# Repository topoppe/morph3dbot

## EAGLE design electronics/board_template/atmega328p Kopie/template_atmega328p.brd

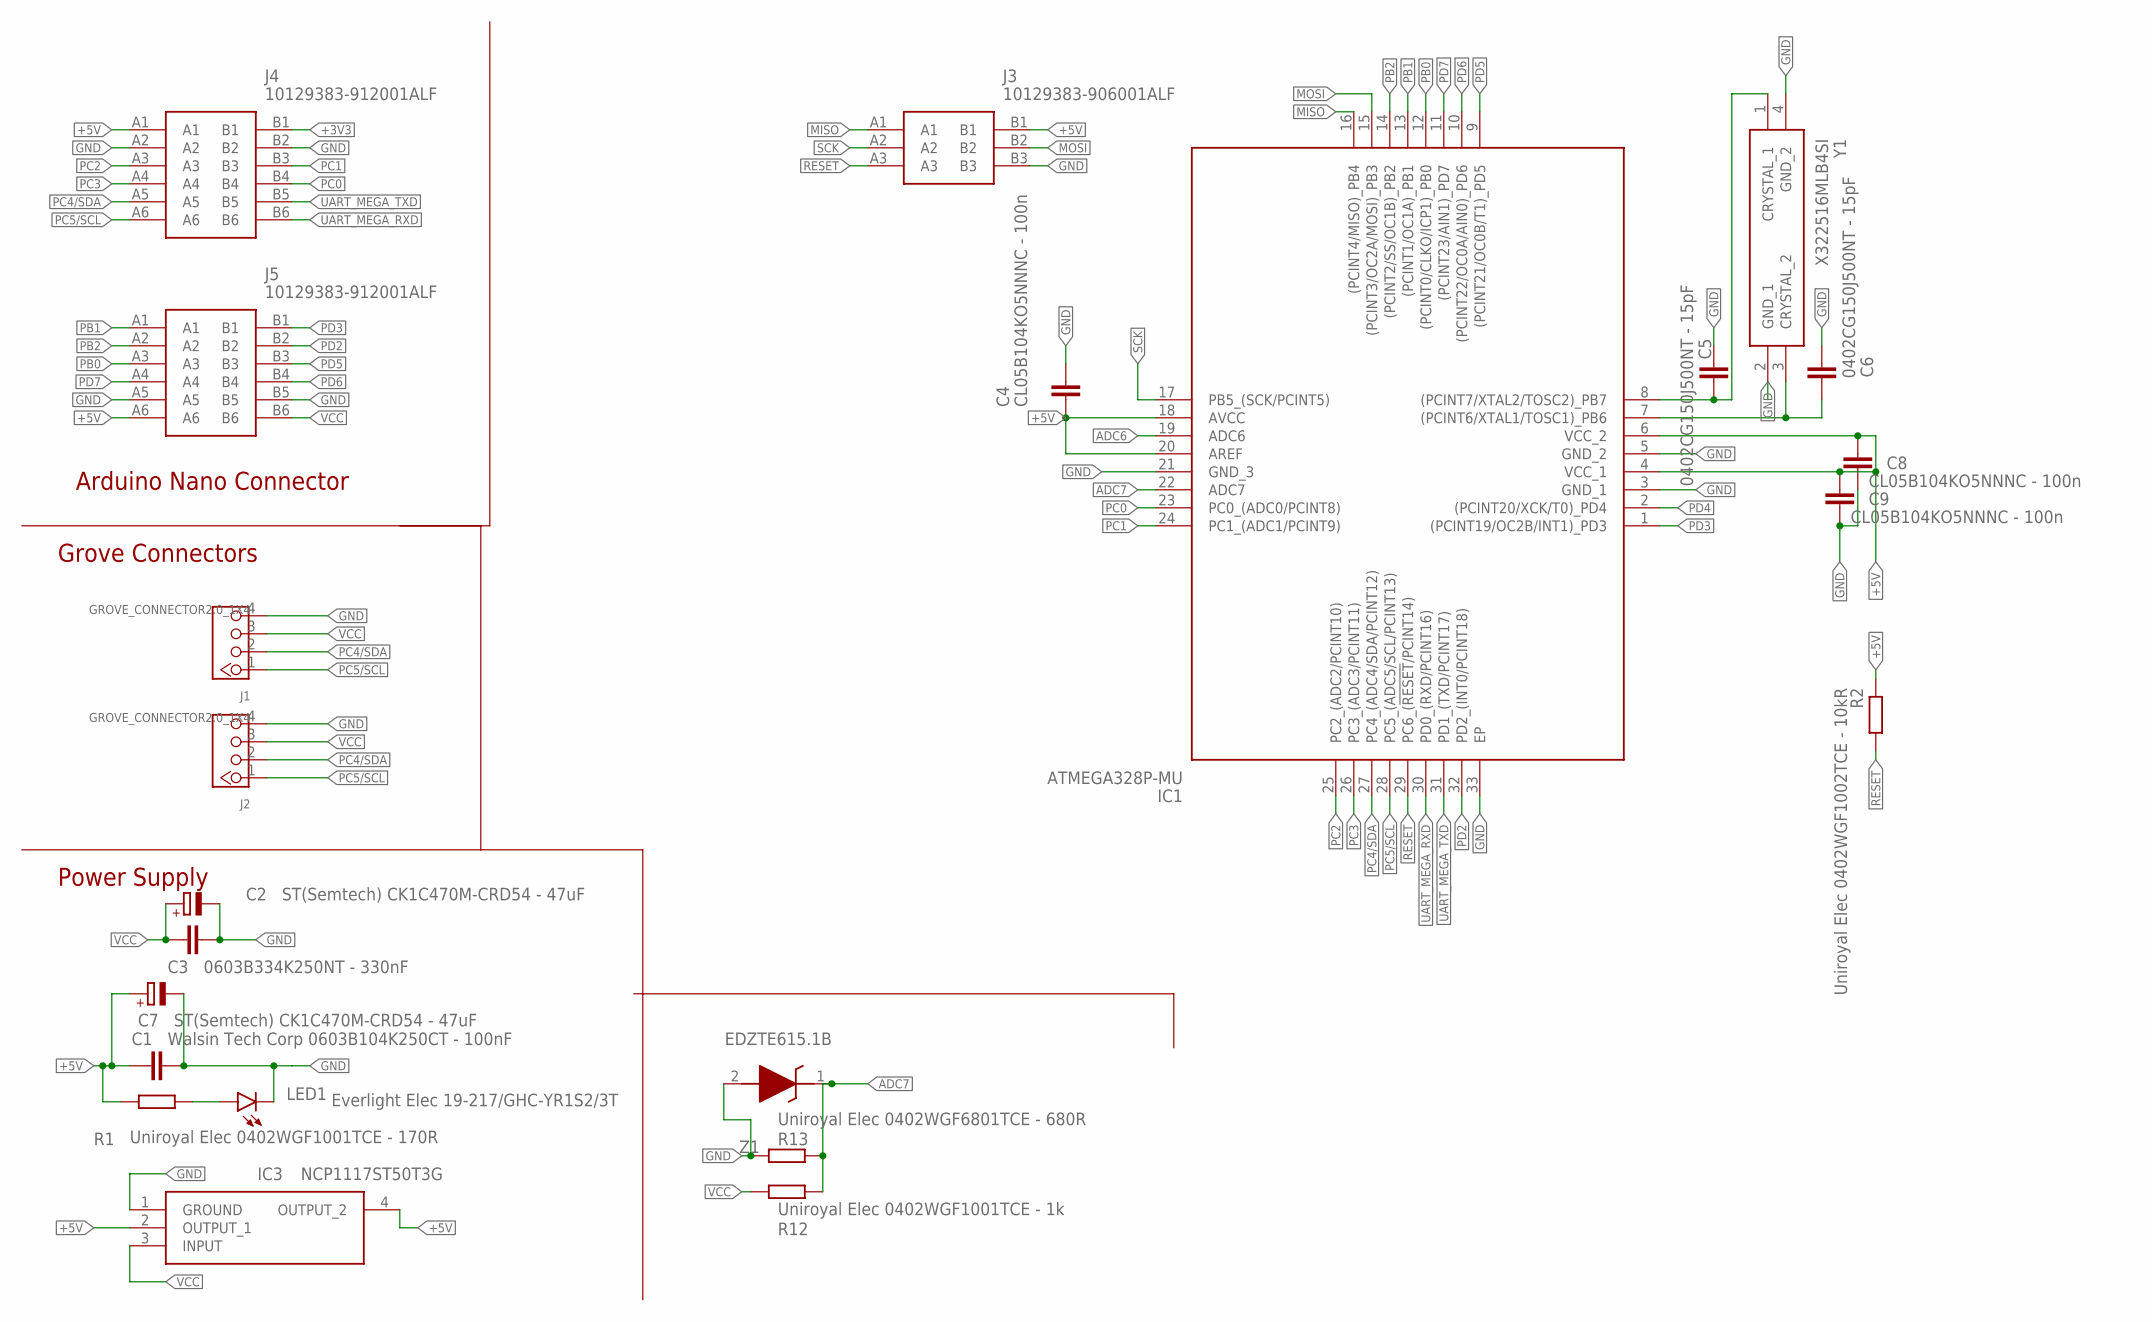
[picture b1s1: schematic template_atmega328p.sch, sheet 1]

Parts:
C1: Walsin Tech Corp 0603B104K250CT - 100nF; C0603
C2, C7: ST(Semtech) CK1C470M-CRD54 - 47uF; PANASONIC_C
C3: 0603B334K250NT - 330nF; C0603
C4, C8, C9: CL05B104KO5NNNC - 100n; C0402
C5, C6: 0402CG150J500NT - 15pF; C0402
IC1: ATMEGA328P-MU; QFN50P500X500X100-33N
IC3: NCP1117ST50T3G; SOT230P700X180-4N@1
J1, J2: GROVE_CONNECTOR2.0_1X4; 2.0_1X4_STRAIGHT
J3: 10129383-906001ALF; 10129383906001ALF
J4, J5: 10129383-912001ALF; 10129383912001ALF
LED1: Everlight Elec 19-217/GHC-YR1S2/3T; CHIPLED_0603
R1: Uniroyal Elec 0402WGF1001TCE - 170R; R0402
R2: Uniroyal Elec 0402WGF1002TCE - 10kR; R0402
R12: Uniroyal Elec 0402WGF1001TCE - 1k; R0402
R13: Uniroyal Elec 0402WGF6801TCE - 680R; R0402
Y1: X322516MLB4SI
Z1: EDZTE615.1B; EMD2

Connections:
+3V3: J4.B1; also elsewhere on the board
+5V: C1.1, C4.1, C7.+, C8.2, C9.2, IC1.4 (VCC_1), IC1.6 (VCC_2), IC1.18 (AVCC), IC1.20 (AREF), IC3.2 (OUTPUT_1), IC3.4 (OUTPUT_2), J3.B1, J4.A1, J5.A6, R1.2, R2.2; also elsewhere on the board
ADC6: IC1.19 (ADC6)
ADC7: IC1.22 (ADC7), R12.1, R13.2, Z1.1 (K)
GND: C1.2, C2.-, C3.1, C4.2, C5.1, C6.1, C7.-, C8.1, C9.1, IC1.3 (GND_1), IC1.5 (GND_2), IC1.21 (GND_3), IC1.33 (EP), IC3.1 (GROUND), J1.4, J2.4, J3.B3, J4.A2, J4.B2, J5.A5, J5.B5, LED1.C, R13.1, Y1.2 (GND_1), Y1.4 (GND_2), Z1.2 (A); also elsewhere on the board
MISO: IC1.16 ((PCINT4/MISO)_PB4), J3.A1
MOSI: IC1.15 ((PCINT3/OC2A/MOSI)_PB3), J3.B2
unnamed: LED1.A, R1.1
unnamed: C5.2, IC1.8 ((PCINT7/XTAL2/TOSC2)_PB7), Y1.1 (CRYSTAL_1)
unnamed: C6.2, IC1.7 ((PCINT6/XTAL1/TOSC1)_PB6), Y1.3 (CRYSTAL_2)
PB0: IC1.12 ((PCINT0/CLKO/ICP1)_PB0), J5.A3
PB1: IC1.13 ((PCINT1/OC1A)_PB1), J5.A1
PB2: IC1.14 ((PCINT2/SS/OC1B)_PB2), J5.A2
PC0: IC1.23 (PC0_(ADC0/PCINT8)), J4.B4
PC1: IC1.24 (PC1_(ADC1/PCINT9)), J4.B3
PC2: IC1.25 (PC2_(ADC2/PCINT10)), J4.A3
PC3: IC1.26 (PC3_(ADC3/PCINT11)), J4.A4
PC4/SDA: IC1.27 (PC4_(ADC4/SDA/PCINT12)), J1.2, J2.2, J4.A5
PC5/SCL: IC1.28 (PC5_(ADC5/SCL/PCINT13)), J1.1, J2.1, J4.A6
PD2: IC1.32 (PD2_(INT0/PCINT18)), J5.B2
PD3: IC1.1 ((PCINT19/OC2B/INT1)_PD3), J5.B1
PD4: IC1.2 ((PCINT20/XCK/T0)_PD4)
PD5: IC1.9 ((PCINT21/OC0B/T1)_PD5), J5.B3
PD6: IC1.10 ((PCINT22/OC0A/AIN0)_PD6), J5.B4
PD7: IC1.11 ((PCINT23/AIN1)_PD7), J5.A4
RESET: IC1.29 (PC6_(!RESET!/PCINT14)), J3.A3, R2.1
SCK: IC1.17 (PB5_(SCK/PCINT5)), J3.A2
UART_MEGA_RXD: IC1.30 (PD0_(RXD/PCINT16)), J4.B6; also elsewhere on the board
UART_MEGA_TXD: IC1.31 (PD1_(TXD/PCINT17)), J4.B5; also elsewhere on the board
VCC: C2.+, C3.2, IC3.3 (INPUT), J1.3, J2.3, J5.B6, R12.2; also elsewhere on the board

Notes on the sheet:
Power Supply
Grove Connectors
Arduino Nano Connector

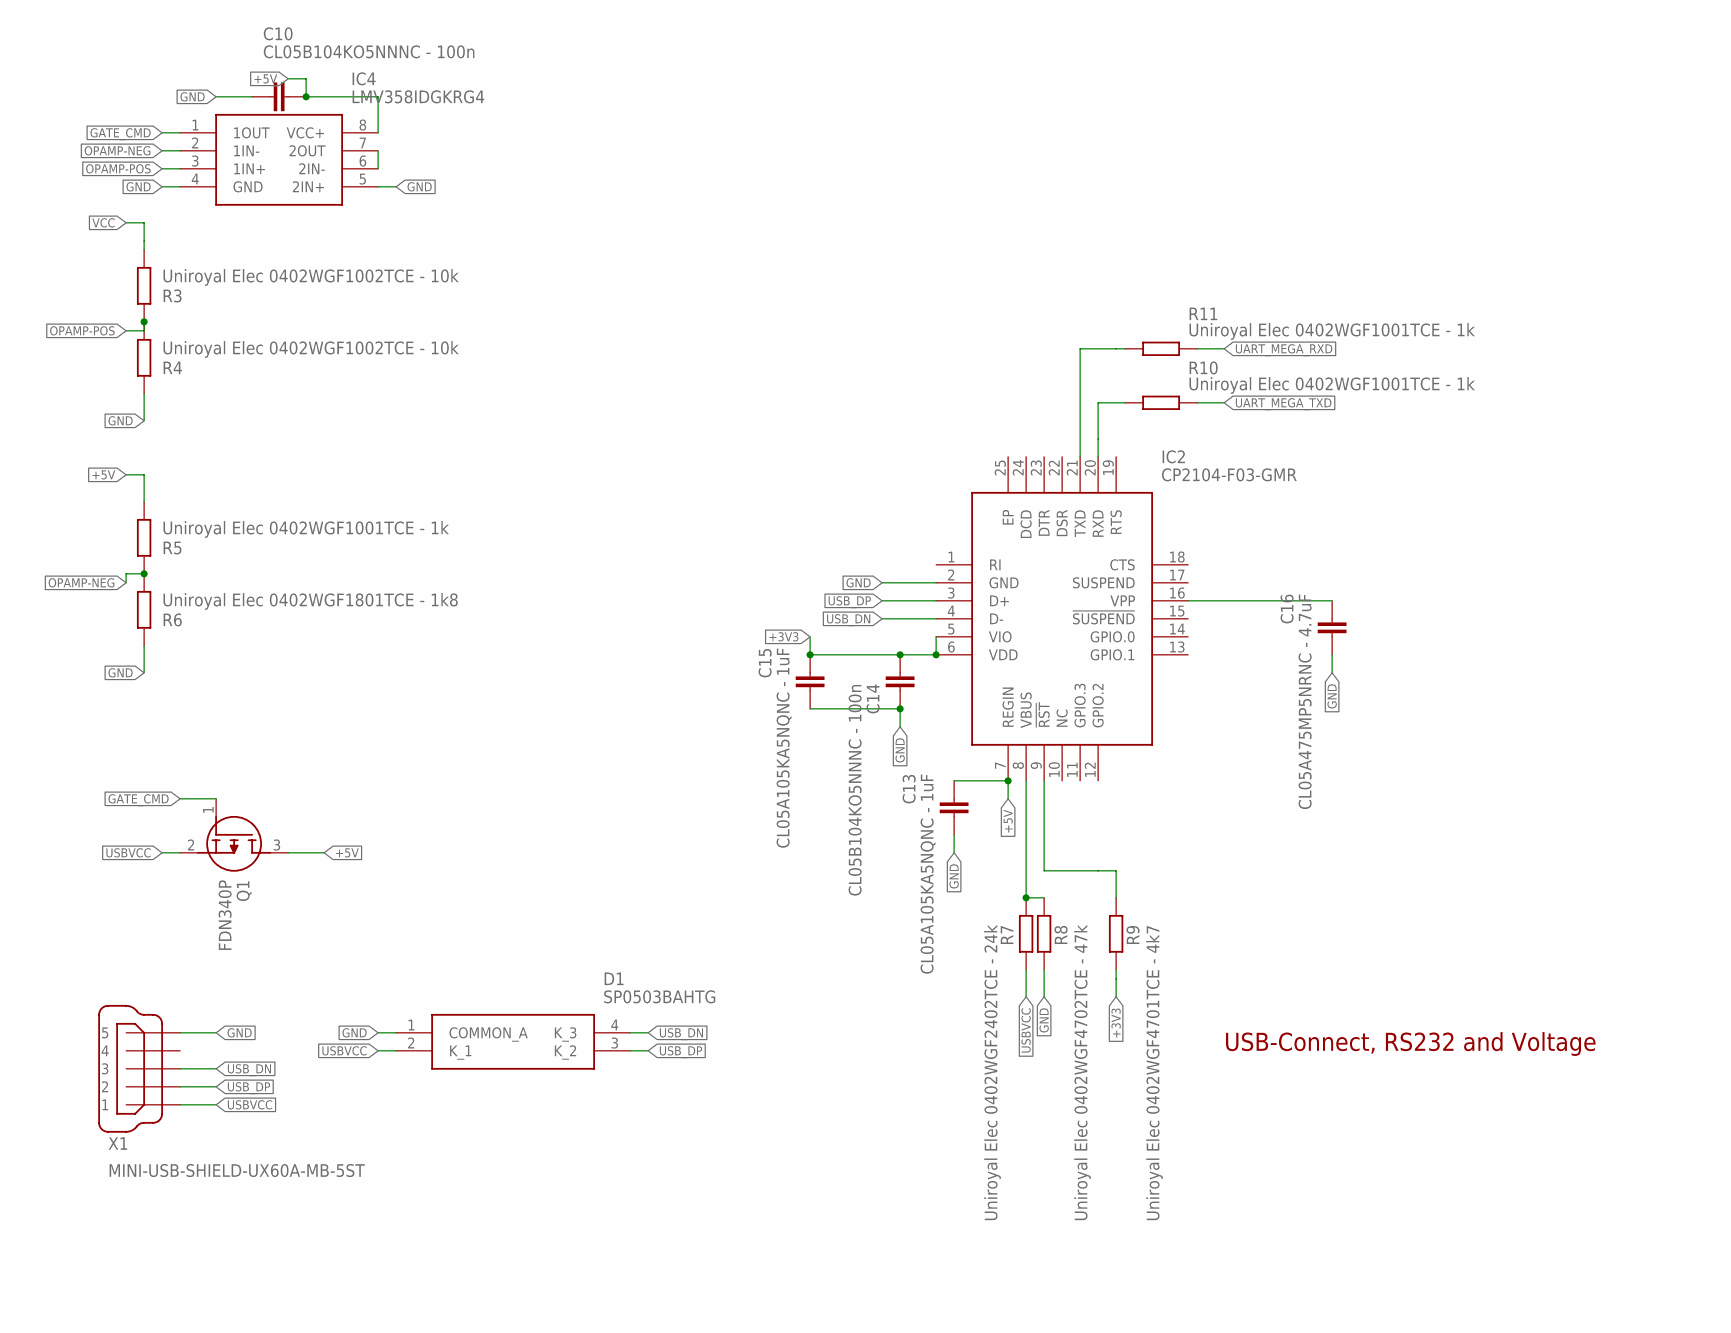
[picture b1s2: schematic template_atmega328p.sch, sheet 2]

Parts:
C10, C14: CL05B104KO5NNNC - 100n; C0402
C13, C15: CL05A105KA5NQNC - 1uF; C0402
C16: CL05A475MP5NRNC - 4.7uF; C0402
D1: SP0503BAHTG
IC2: CP2104-F03-GMR; QFN50P400X400X80-25N
IC4: LMV358IDGKRG4; SOP65P490X110-8N
Q1: FDN340P; SOT95P237X112-3N
R3, R4: Uniroyal Elec 0402WGF1002TCE - 10k; R0402
R5, R10, R11: Uniroyal Elec 0402WGF1001TCE - 1k; R0402
R6: Uniroyal Elec 0402WGF1801TCE - 1k8; R0402
R7: Uniroyal Elec 0402WGF2402TCE - 24k; R0402
R8: Uniroyal Elec 0402WGF4702TCE - 47k; R0402
R9: Uniroyal Elec 0402WGF4701TCE - 4k7; R0402
X1: MINI-USB-SHIELD-UX60A-MB-5ST; UX60A-MB-5ST

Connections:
+3V3: C14.2, C15.2, IC2.5 (VIO), IC2.6 (VDD), R9.2; also elsewhere on the board
+5V: C10.2, C13.2, IC2.7 (REGIN), IC4.8 (VCC+), Q1.3 (D), R5.1; also elsewhere on the board
GATE_CMD: IC4.1 (1OUT), Q1.1 (G)
GND: C10.1, C13.1, C14.1, C15.1, C16.1, D1.1 (COMMON_A), IC2.2 (GND), IC4.4 (GND), IC4.5 (2IN+), R4.2, R6.2, R8.2, X1.5; also elsewhere on the board
unnamed: IC4.6 (2IN-), IC4.7 (2OUT)
unnamed: IC2.8 (VBUS), R7.1, R8.1
unnamed: IC2.9 (!RST), R9.1
unnamed: C16.2, IC2.16 (VPP)
unnamed: IC2.21 (TXD), R11.1
unnamed: IC2.20 (RXD), R10.1
OPAMP-NEG: IC4.2 (1IN-), R5.2, R6.1
OPAMP-POS: IC4.3 (1IN+), R3.2, R4.1
UART_MEGA_RXD: R11.2; also elsewhere on the board
UART_MEGA_TXD: R10.2; also elsewhere on the board
USBVCC: D1.2 (K_1), Q1.2 (S), R7.2, X1.1
USB_DN: D1.4 (K_3), IC2.4 (D-), X1.3
USB_DP: D1.3 (K_2), IC2.3 (D+), X1.2
VCC: R3.1; also elsewhere on the board

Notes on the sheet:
USB-Connect, RS232 and Voltage

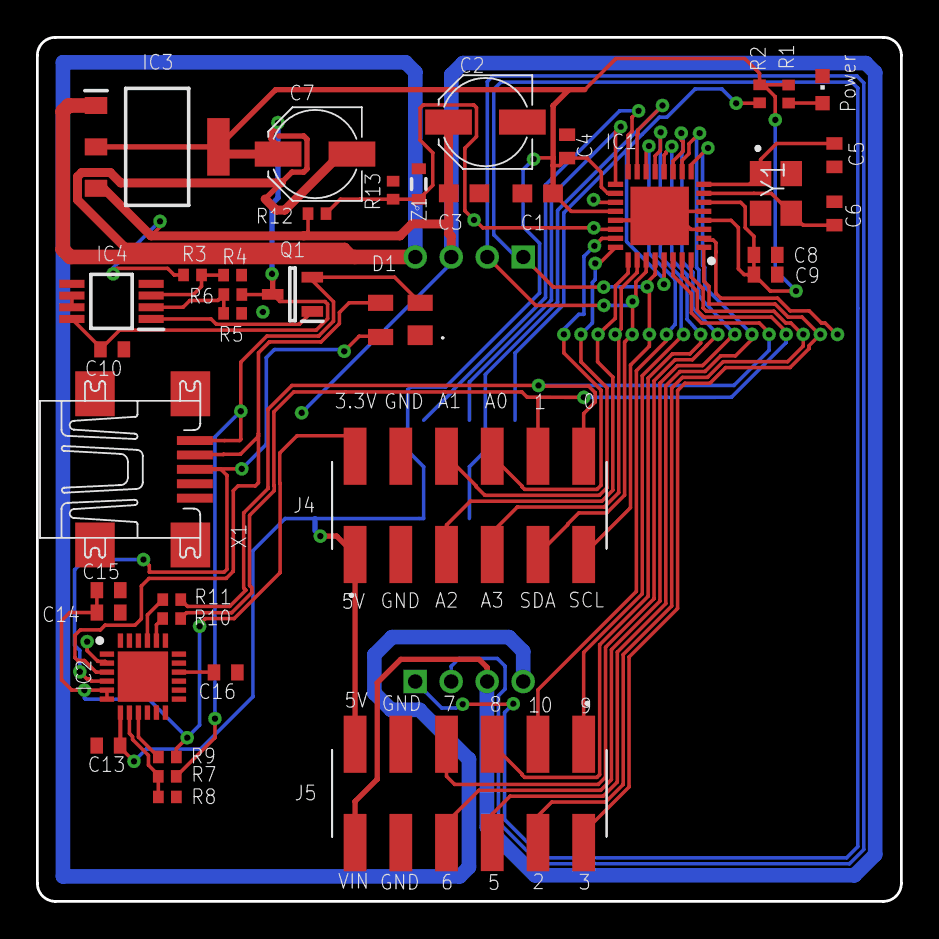
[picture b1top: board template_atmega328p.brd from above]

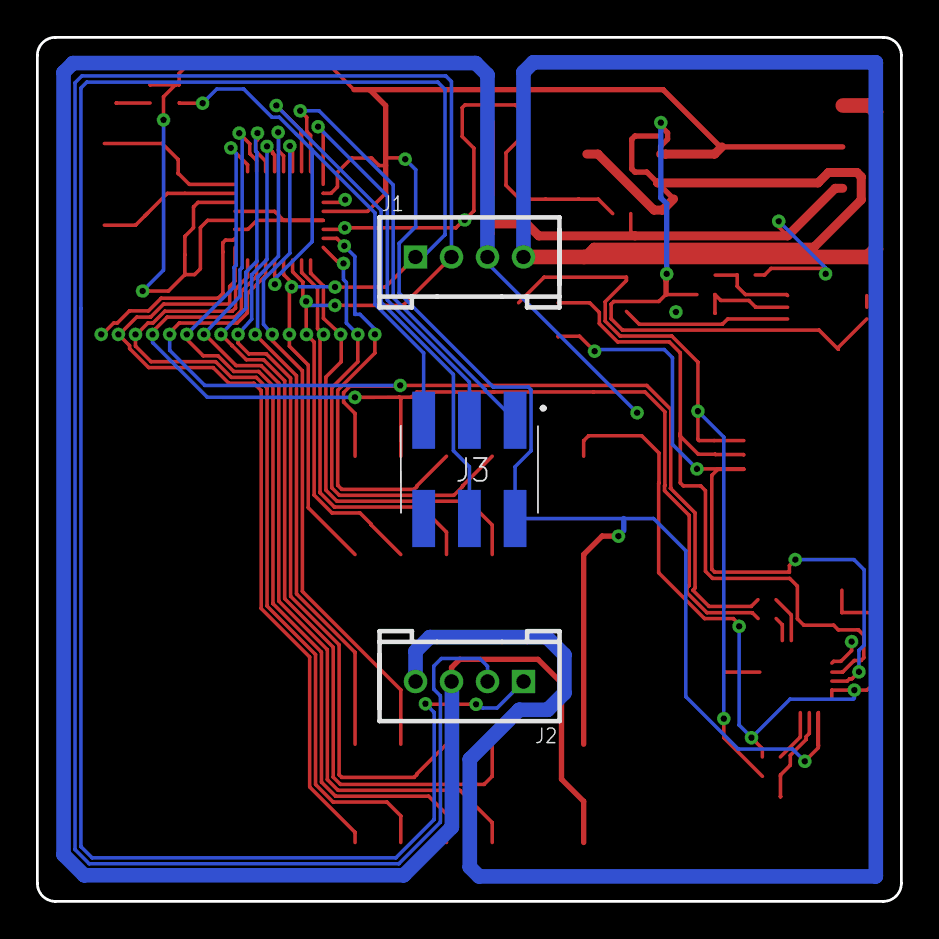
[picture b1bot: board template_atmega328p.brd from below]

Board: 2 copper layers, 48.0 x 48.0 mm, 42 parts (3 on the bottom side), 40 nets.

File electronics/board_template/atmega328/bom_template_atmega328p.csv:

"Qty";"Value";"Device";"Package";"Parts";"Description";"ARROW_PART_NUMBER";"ARROW_PRICE-STOCK";"DESCRIPTION";"HEIGHT";"MANUFACTURER_NAME";"MANUFACTURER_PART_NUMBER";"MF";"MOUSER_PART_NUMBER";"MOUSER_PRICE-STOCK";"MPN";"OC_FARNELL";"OC_NEWARK";"POPULARITY";"SPICEPREFIX";
"2";"0402CG150J500NT - 15pF";"C-EUC0402";"C0402";"C5, C6";"CAPACITOR, European symbol";"";"";"";"";"";"";"";"";"";"";"";"";"18";"C";
"1";"0603B334K250NT - 330nF";"C-EUC0603";"C0603";"C3";"CAPACITOR, European symbol";"";"";"";"";"";"";"";"";"";"";"";"";"73";"C";
"1";"10129383-906001ALF";"10129383-906001ALF";"10129383906001ALF";"J3";"Headers & Wire Housings ECONOSTIK HEADER DR VT SMT 2X3";"10129383-906001ALF";"https://www.arrow.com/en/products/10129383-906001alf/amphenol-fci";"Headers & Wire Housings ECONOSTIK HEADER DR VT SMT 2X3";"8.58mm";"Amphenol";"10129383-906001ALF";"";"649-1012938390601ALF";"https://www.mouser.co.uk/ProductDetail/Amphenol-FCI/10129383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";"";"";"";"";"";
"2";"10129383-912001ALF";"10129383-912001ALF";"10129383912001ALF";"J4, J5";"EconoStik, Board to Board connector, Unshrouded Vertical Header, Surface Mount, Double Row,  Positions, 2.54 mm (0.100in) Pitch.";"";"";"EconoStik, Board to Board connector, Unshrouded Vertical Header, Surface Mount, Double Row,  Positions, 2.54 mm (0.100in) Pitch.";"8.58mm";"Amphenol";"10129383-912001ALF";"";"649-1012938391201ALF";"https://www.mouser.co.uk/ProductDetail/Amphenol-FCI/10129383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";"";"";"";"";"";
"1";"ATMEGA328P-MU";"ATMEGA328P-MU";"QFN50P500X500X100-33N";"IC1";"ATMEGA328P-MU, 8 bit AVR Microcontroller 20MHz 1, 32kb Flash, 2kb RAM, I2C SPI 32-Pin MLF";"ATMEGA328P-MU";"https://www.arrow.com/en/products/atmega328p-mu/microchip-te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";"ATMEGA328P-MU, 8 bit AVR Microcontroller 20MHz 1, 32kb Flash, 2kb RAM, I2C SPI 32-Pin MLF";"1mm";"Microchip";"ATMEGA328P-MU";"";"556-ATMEGA328P-MU";"https://www.mouser.co.uk/ProductDetail/Microchip-Technology-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";"";"";"";"";"";
"2";"CL05A105KA5NQNC - 1uF";"C-EUC0402";"C0402";"C13, C15";"CAPACITOR, European symbol";"";"";"";"";"";"";"";"";"";"";"";"";"18";"C";
"1";"CL05A475MP5NRNC - 4.7uF";"C-EUC0402";"C0402";"C16";"CAPACITOR, European symbol";"";"";"";"";"";"";"";"";"";"";"";"";"18";"C";
"6";"CL05B104KO5NNNC - 100n";"C-EUC0402";"C0402";"C4, C8, C9, C10, C11, C14";"CAPACITOR, European symbol";"";"";"";"";"";"";"";"";"";"";"";"";"18";"C";
"1";"CP2104-F03-GMR";"CP2104-F03-GMR";"QFN50P400X400X80-25N";"IC2";"USB-to-UART 1-CH 576byte FIFO 3.3V Automotive 24-Pin QFN EP T/R";"CP2104-F03-GMR";"https://www.arrow.com/en/products/cp2104-f03-gmr/silicon-labs";"USB-to-UART 1-CH 576byte FIFO 3.3V Automotive 24-Pin QFN EP T/R";"0.8mm";"Silicon Labs";"CP2104-F03-GMR";"";"634-CP2104-F03-GMR";"https://www.mouser.co.uk/ProductDetail/Silicon-Labs/CP2104-F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";"";"";"";"";"";
"1";"EDZTE615.1B";"EDZTE615.1B";"EMD2";"Z1";"ROHM EDZTE615.1B Zener Diode, 5.1V 2% 0.1 W SMT 2-Pin EMD";"";"";"ROHM EDZTE615.1B Zener Diode, 5.1V 2% 0.1 W SMT 2-Pin EMD";"mm";"ROHM Semiconductor";"EDZTE615.1B";"";"755-EDZTE615.1B";"https://www.mouser.co.uk/ProductDetail/ROHM-Semiconductor/ED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";"";"";"";"";"";
"1";"Everlight Elec 19-217/GHC-YR1S2/3T";"LEDCHIPLED_0603";"CHIPLED_0603";"LED1";"LED";"";"";"";"";"";"";"";"";"";"";"";"";"28";"";
"1";"FDN340P";"FDN340P";"SOT95P237X112-3N";"Q1";"Trans MOSFET P-CH 20V 2A 3-Pin SuperSOT";"FDN340P";"https://www.arrow.com/en/products/fdn340p/on-semiconductor";"Trans MOSFET P-CH 20V 2A 3-Pin SuperSOT";"1.12mm";"ON Semiconductor";"FDN340P";"";"512-FDN340P";"https://www.mouser.co.uk/ProductDetail/ON-Semiconductor-Fair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";"";"";"";"";"";
"2";"GROVE_CONNECTOR2.0_1X4";"GROVE_CONNECTOR2.0_1X4";"2.0_1X4_STRAIGHT";"J1, J2";"Seeedstudio Grove-Connector:";"";"";"";"";"";"";"";"";"";"";"";"";"";"";
"1";"LMV358IDGKRG4";"LMV358IDGKRG4";"SOP65P490X110-8N";"IC4";"Operational Amplifiers - Op Amps Dual Low-Voltage Rail-to-Rail Out";"LMV358IDGKRG4";"https://www.arrow.com/en/products/lmv358idgkrg4/texas-instruments";"Operational Amplifiers - Op Amps Dual Low-Voltage Rail-to-Rail Out";"1.1mm";"Texas Instruments";"LMV358IDGKRG4";"";"595-LMV358IDGKRG4";"https://www.mouser.co.uk/ProductDetail/Texas-Instruments/LMV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";"";"";"";"";"";
"1";"LOGO_MORPHBOT5MM";"LOGO_MORPHBOT5MM";"LOGO_MORPHBOT";"U$1";"";"";"";"";"";"";"";"";"";"";"";"";"";"";"";
"1";"MINI-USB-SHIELD-UX60A-MB-5ST";"MINI-USB-SHIELD-UX60A-MB-5ST";"UX60A-MB-5ST";"X1";"MINI USB Connector";"";"";"";"";"";"";"";"";"";"";"unknown";"unknown";"0";"";
"1";"NCP1117ST50T3G";"NCP1117ST50T3G";"SOT230P700X180-4N";"IC3";"ON SEMICONDUCTOR - NCP1117ST50T3G - LDO, REG, 20VIN, 1A, 5V, 1%, SOT223-3";"NCP1117ST50T3G";"https://www.arrow.com/en/products/ncp1117st50t3g/on-semiconductor";"ON SEMICONDUCTOR - NCP1117ST50T3G - LDO, REG, 20VIN, 1A, 5V, 1%, SOT223-3";"1.8mm";"ON Semiconductor";"NCP1117ST50T3G";"";"863-NCP1117ST50T3G";"https://www.mouser.co.uk/ProductDetail/ON-Semiconductor/NCP1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";"";"";"";"";"";
"3";"OPEN-PNP-FIDUCIAL";"OPEN-PNP-FIDUCIAL";"OPEN-PNP-FIDUCIAL";"FID1, FID2, FID3";"";"";"";"";"";"";"";"";"";"";"";"";"";"";"";
"1";"SP0503BAHTG";"SP0503BAHTG";"SP0503BAHTG";"D1";"ESD Suppressors / TVS Diodes TVS AVAL DIODE SMT";"SP0503BAHTG";"https://www.arrow.com/en/products/sp0503bahtg/littelfuse";"ESD Suppressors / TVS Diodes TVS AVAL DIODE SMT";"1.22mm";"LITTELFUSE";"SP0503BAHTG";"";"576-SP0503BAHTG";"https://www.mouser.co.uk/ProductDetail/Littelfuse/SP0503BAHT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";"";"";"";"";"";
"2";"ST(Semtech) CK1C470M-CRD54 - 47uF";"CPOL-EUC";"PANASONIC_C";"C2, C7";"POLARIZED CAPACITOR, European symbol";"";"";"";"";"";"";"";"";"";"";"";"";"4";"C";
"1";"Uniroyal Elec 0402WGF1001TCE - 170R";"R-EU_R0402";"R0402";"R1";"RESISTOR, European symbol";"";"";"";"";"";"";"";"";"";"";"";"";"0";"R";
"4";"Uniroyal Elec 0402WGF1001TCE - 1k";"R-EU_R0402";"R0402";"R5, R10, R11, R12";"RESISTOR, European symbol";"";"";"";"";"";"";"";"";"";"";"";"";"0";"R";
"2";"Uniroyal Elec 0402WGF1002TCE - 10k";"R-EU_R0402";"R0402";"R3, R4";"RESISTOR, European symbol";"";"";"";"";"";"";"";"";"";"";"";"";"0";"R";
"1";"Uniroyal Elec 0402WGF1002TCE - 10kR";"R-EU_R0402";"R0402";"R2";"RESISTOR, European symbol";"";"";"";"";"";"";"";"";"";"";"";"";"0";"R";
"1";"Uniroyal Elec 0402WGF1801TCE - 1k8";"R-EU_R0402";"R0402";"R6";"RESISTOR, European symbol";"";"";"";"";"";"";"";"";"";"";"";"";"0";"R";
"1";"Uniroyal Elec 0402WGF2402TCE - 24k";"R-EU_R0402";"R0402";"R7";"RESISTOR, European symbol";"";"";"";"";"";"";"";"";"";"";"";"";"0";"R";
"1";"Uniroyal Elec 0402WGF4701TCE - 4k7";"R-EU_R0402";"R0402";"R9";"RESISTOR, European symbol";"";"";"";"";"";"";"";"";"";"";"";"";"0";"R";
"1";"Uniroyal Elec 0402WGF4702TCE - 47k";"R-EU_R0402";"R0402";"R8";"RESISTOR, European symbol";"";"";"";"";"";"";"";"";"";"";"";"";"0";"R";
"1";"Uniroyal Elec 0402WGF6801TCE - 680R";"R-EU_R0402";"R0402";"R13";"RESISTOR, European symbol";"";"";"";"";"";"";"";"";"";"";"";"";"0";"R";
"1";"Walsin Tech Corp 0603B104K250CT - 100nF";"C-EUC0603";"C0603";"C1";"CAPACITOR, European symbol";"";"";"";"";"";"";"";"";"";"";"";"";"73";"C";
"1";"X322516MLB4SI";"X322516MLB4SI";"X322516MLB4SI";"Y1";"Crystal";"";"";"Crystal";"0.8mm";"Yangxing Tech";"X322516MLB4SI";"";"";"";"";"";"";"";"";

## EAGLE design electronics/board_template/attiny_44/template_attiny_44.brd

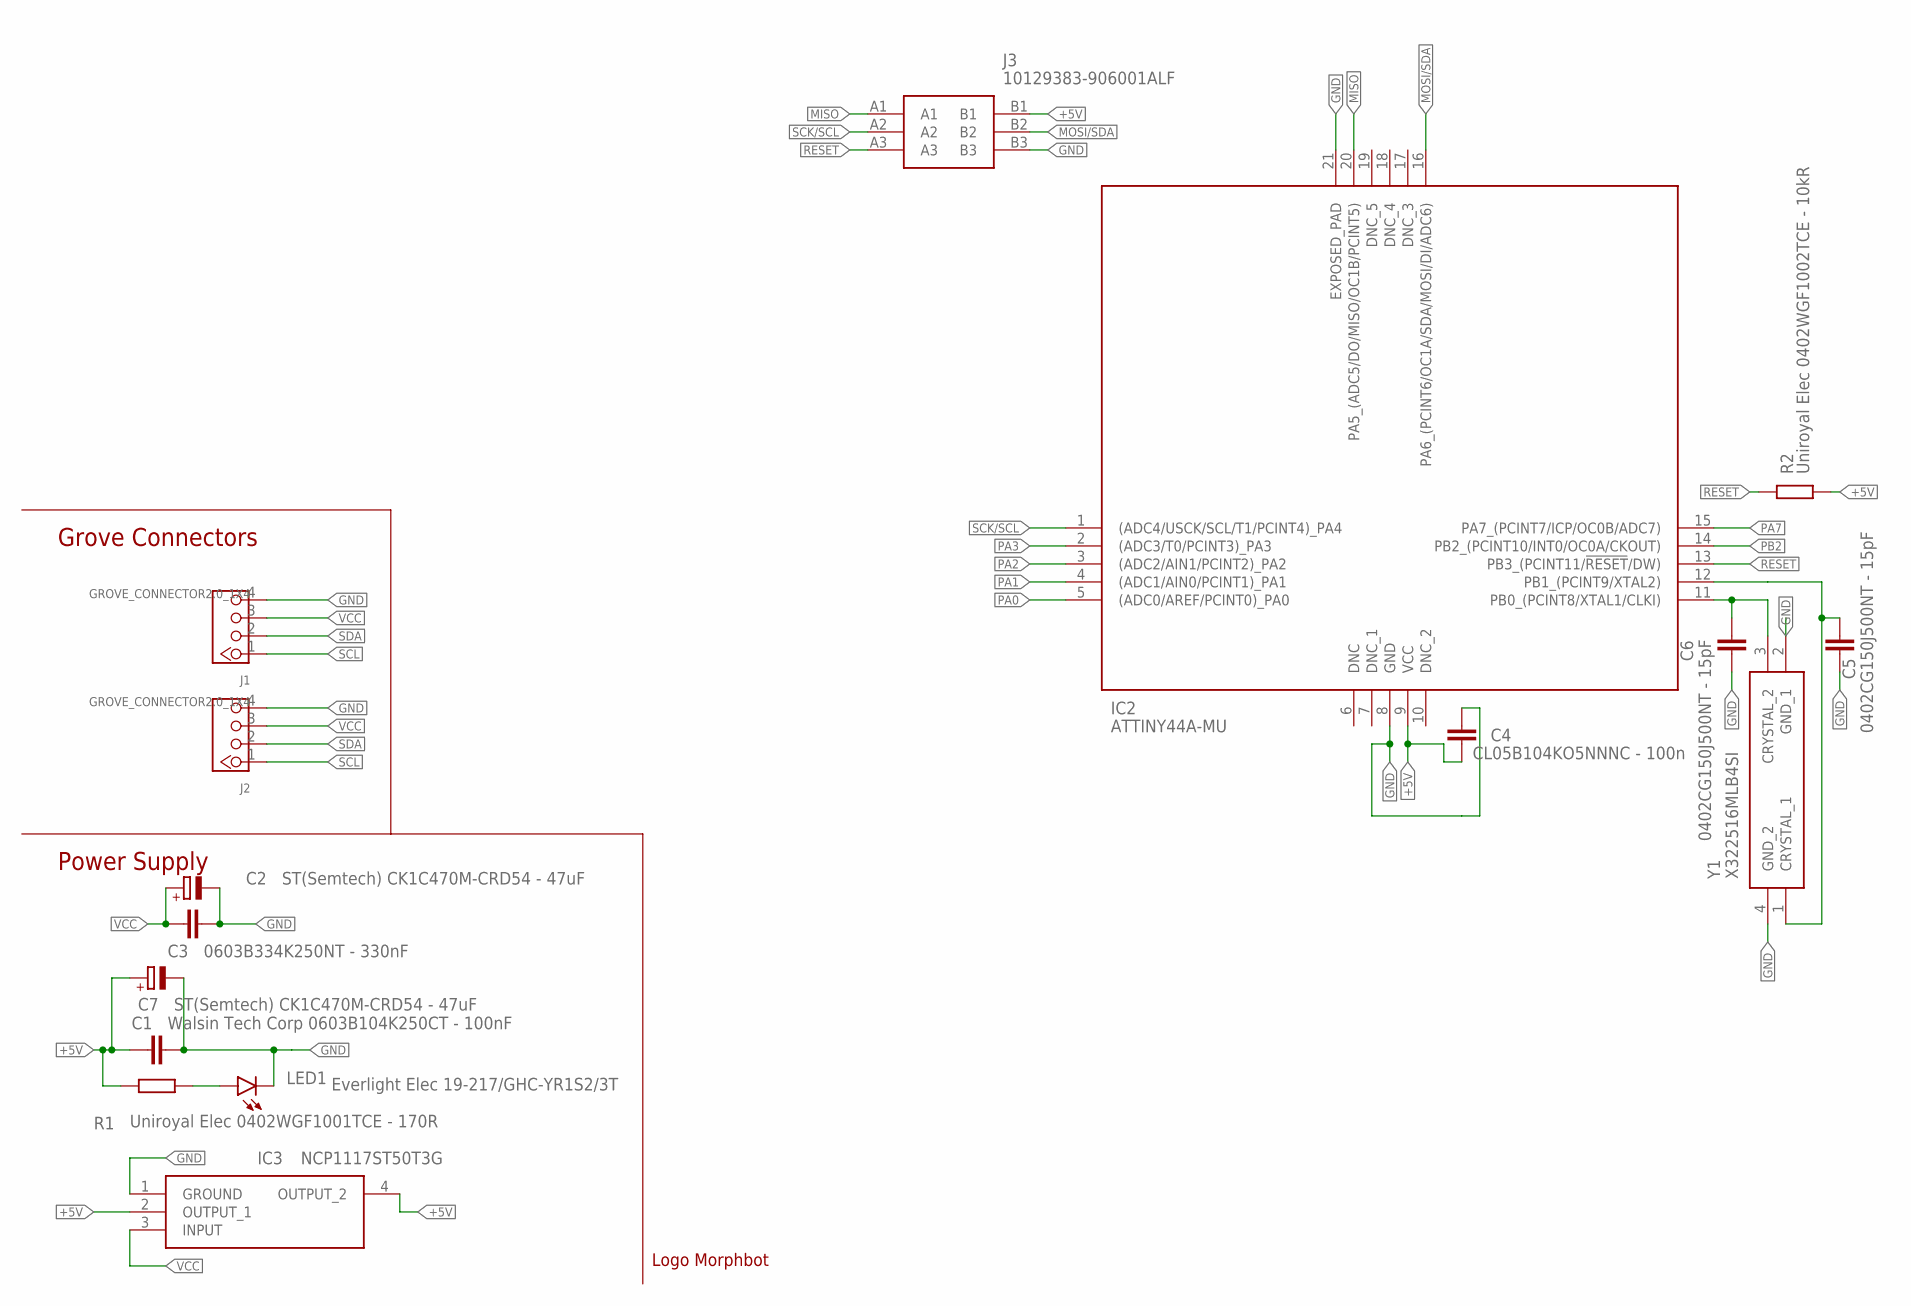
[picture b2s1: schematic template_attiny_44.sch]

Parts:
C1: Walsin Tech Corp 0603B104K250CT - 100nF; C0603
C2, C7: ST(Semtech) CK1C470M-CRD54 - 47uF; PANASONIC_C
C3: 0603B334K250NT - 330nF; C0603
C4: CL05B104KO5NNNC - 100n; C0402
C5, C6: 0402CG150J500NT - 15pF; C0402
IC2: ATTINY44A-MU; QFN50P400X400X80-21N
IC3: NCP1117ST50T3G; SOT230P700X180-4N
J1, J2: GROVE_CONNECTOR2.0_1X4; 2.0_1X4_STRAIGHT
J3: 10129383-906001ALF; 10129383906001ALF
LED1: Everlight Elec 19-217/GHC-YR1S2/3T; CHIPLED_0603
R1: Uniroyal Elec 0402WGF1001TCE - 170R; R0402
R2: Uniroyal Elec 0402WGF1002TCE - 10kR; R0402
U$1: LOGO_MORPHBOT5MM; LOGO_MORPHBOT
Y1: X322516MLB4SI

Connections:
+5V: C1.1, C4.1, C7.+, IC2.9 (VCC), IC3.2 (OUTPUT_1), IC3.4 (OUTPUT_2), J3.B1, R1.2, R2.2
GND: C1.2, C2.-, C3.1, C4.2, C5.1, C6.1, C7.-, IC2.8 (GND), IC2.21 (EXPOSED_PAD), IC3.1 (GROUND), J1.4, J2.4, J3.B3, LED1.C, Y1.2 (GND_1), Y1.4 (GND_2)
MISO: IC2.20 (PA5_(ADC5/DO/MISO/OC1B/PCINT5)), J3.A1
MOSI/SDA: IC2.16 (PA6_(PCINT6/OC1A/SDA/MOSI/DI/ADC6)), J3.B2
unnamed: LED1.A, R1.1
unnamed: C5.2, IC2.12 (PB1_(PCINT9/XTAL2)), Y1.1 (CRYSTAL_1)
unnamed: C6.2, IC2.11 (PB0_(PCINT8/XTAL1/CLKI)), Y1.3 (CRYSTAL_2)
PA0: IC2.5 ((ADC0/AREF/PCINT0)_PA0)
PA1: IC2.4 ((ADC1/AIN0/PCINT1)_PA1)
PA2: IC2.3 ((ADC2/AIN1/PCINT2)_PA2)
PA3: IC2.2 ((ADC3/T0/PCINT3)_PA3)
PA7: IC2.15 (PA7_(PCINT7/ICP/OC0B/ADC7))
PB2: IC2.14 (PB2_(PCINT10/INT0/OC0A/CKOUT))
RESET: IC2.13 (PB3_(PCINT11/!RESET!/DW)), J3.A3, R2.1
SCK/SCL: IC2.1 ((ADC4/USCK/SCL/T1/PCINT4)_PA4), J3.A2
SCL: J1.1, J2.1
SDA: J1.2, J2.2
VCC: C2.+, C3.2, IC3.3 (INPUT), J1.3, J2.3

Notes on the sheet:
Power Supply
Grove Connectors

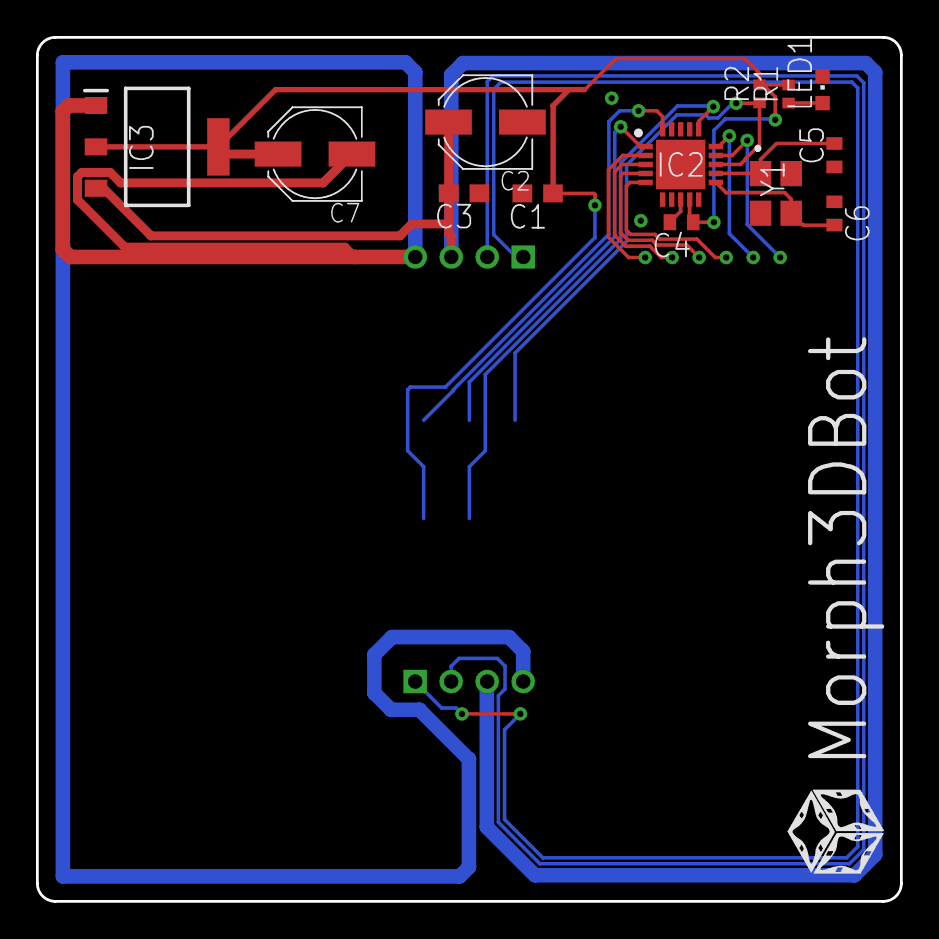
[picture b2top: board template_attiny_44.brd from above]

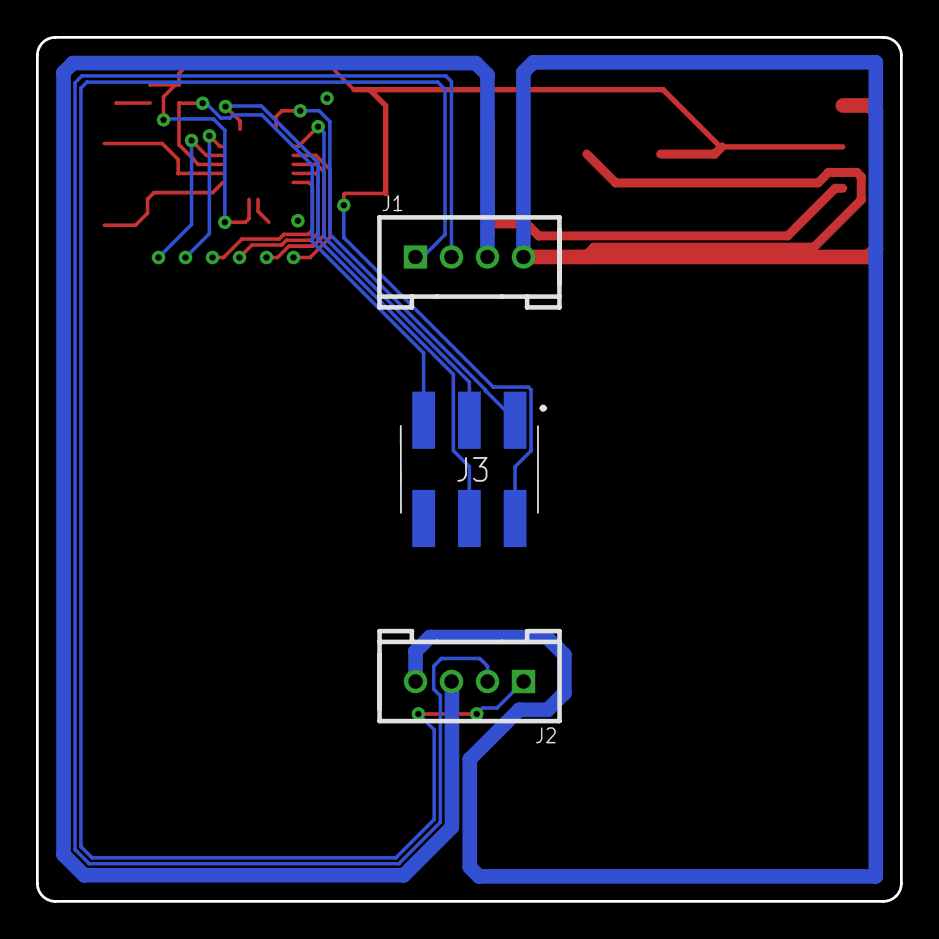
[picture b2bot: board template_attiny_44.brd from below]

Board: 2 copper layers, 48.0 x 48.0 mm, 17 parts (3 on the bottom side), 12 nets.

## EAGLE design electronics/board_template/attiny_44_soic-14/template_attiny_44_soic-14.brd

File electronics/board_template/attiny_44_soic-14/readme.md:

# ATTiny-SOIC Board Template

Das Template für die ATTiny-Platine ist ausgestattet mit einem ATTiny-44 Controller der Firma Microchip.
Die Platine selbst stellt keine Funktion dar, sondern dient als Vorlage für eigene Boards.

## Spannungsversorgung
Auf der Platine ist ein Linearregler verbaut. Er erzeugt aus der Versorgungsspannung des Systems eine stabile 5V Spannungsversorgung für den Controller sowie weitere Peripherie.

## Programmierschnittstelle
Auf der Rückseite der Platine befindet sich eine ICSP-Schnittstelle mit Arduino-typischer Belegung

## Controller
Der ATtiny-Controller auf dieser Platine ist im SOIC-Gehäuse verbaut. Eine Bestückung per Hand ist auch ungeübten Lötern möglich.

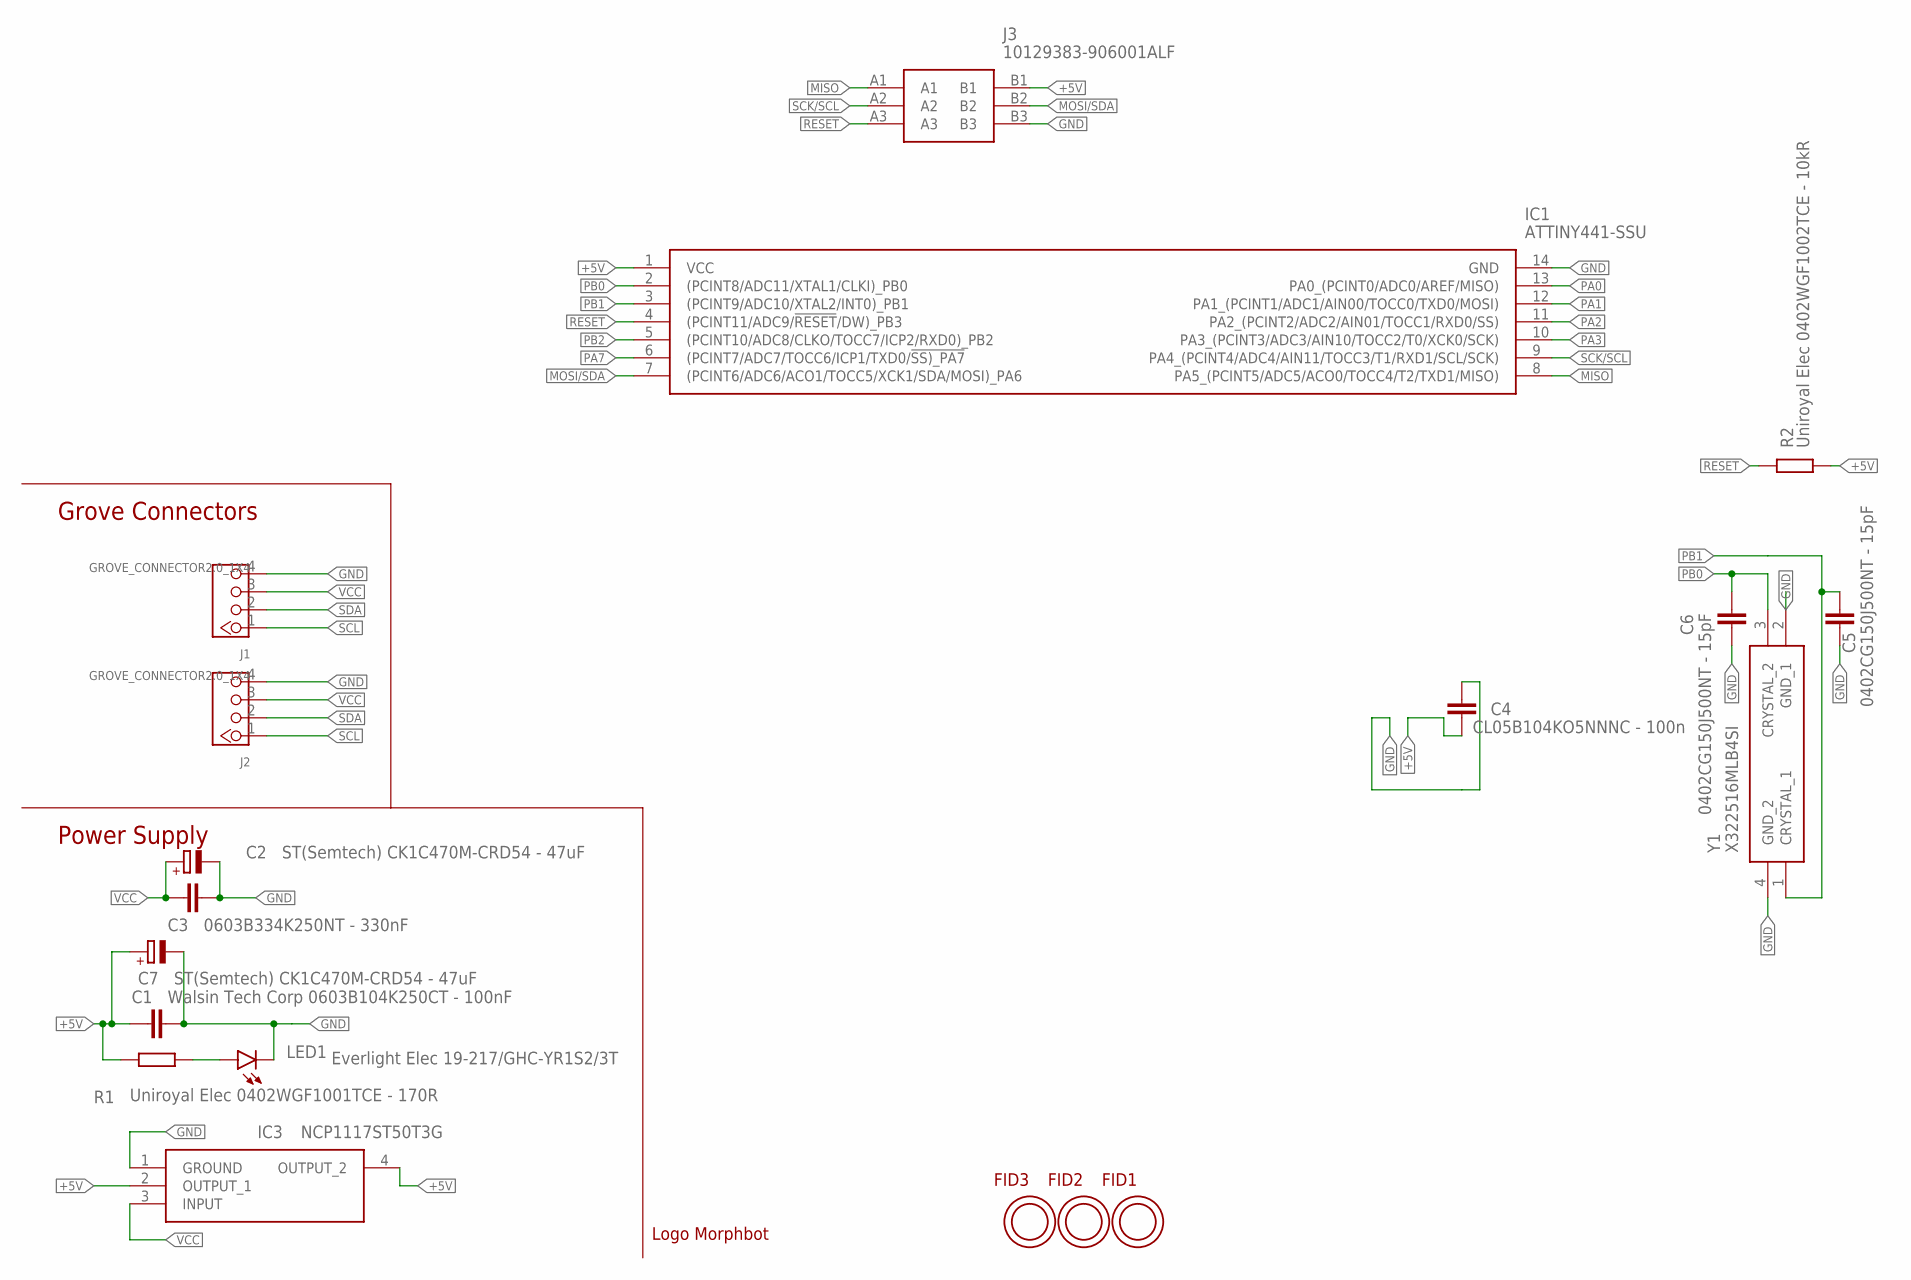
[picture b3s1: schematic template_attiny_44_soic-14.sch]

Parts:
C1: Walsin Tech Corp 0603B104K250CT - 100nF; C0603
C2, C7: ST(Semtech) CK1C470M-CRD54 - 47uF; PANASONIC_C
C3: 0603B334K250NT - 330nF; C0603
C4: CL05B104KO5NNNC - 100n; C0402
C5, C6: 0402CG150J500NT - 15pF; C0402
FID1, FID2, FID3: OPEN-PNP-FIDUCIAL
IC1: ATTINY441-SSU; SOIC127P600X175-14N
IC3: NCP1117ST50T3G; SOT230P700X180-4N
J1, J2: GROVE_CONNECTOR2.0_1X4; 2.0_1X4_STRAIGHT
J3: 10129383-906001ALF; 10129383906001ALF
LED1: Everlight Elec 19-217/GHC-YR1S2/3T; CHIPLED_0603
R1: Uniroyal Elec 0402WGF1001TCE - 170R; R0402
R2: Uniroyal Elec 0402WGF1002TCE - 10kR; R0402
U$1: LOGO_MORPHBOT5MM; LOGO_MORPHBOT
Y1: X322516MLB4SI

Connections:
+5V: C1.1, C4.1, C7.+, IC1.1 (VCC), IC3.2 (OUTPUT_1), IC3.4 (OUTPUT_2), J3.B1, R1.2, R2.2
GND: C1.2, C2.-, C3.1, C4.2, C5.1, C6.1, C7.-, IC1.14 (GND), IC3.1 (GROUND), J1.4, J2.4, J3.B3, LED1.C, Y1.2 (GND_1), Y1.4 (GND_2)
MISO: IC1.8 (PA5_(PCINT5/ADC5/ACO0/TOCC4/T2/TXD1/MIS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), J3.A1
MOSI/SDA: IC1.7 ((PCINT6/ADC6/ACO1/TOCC5/XCK1/SDA/MOSI)_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), J3.B2
unnamed: LED1.A, R1.1
PA0: IC1.13 (PA0_(PCINT0/ADC0/AREF/MISO))
PA1: IC1.12 (PA1_(PCINT1/ADC1/AIN00/TOCC0/TXD0/MOSI))
PA2: IC1.11 (PA2_(PCINT2/ADC2/AIN01/TOCC1/RXD0/SS))
PA3: IC1.10 (PA3_(PCINT3/ADC3/AIN10/TOCC2/T0/XCK0/SC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)
PA7: IC1.6 ((PCINT7/ADC7/TOCC6/ICP1/TXD0/!SS)_PA7)
PB0: C6.2, IC1.2 ((PCINT8/ADC11/XTAL1/CLKI)_PB0), Y1.3 (CRYSTAL_2)
PB1: C5.2, IC1.3 ((PCINT9/ADC10/XTAL2/INT0)_PB1), Y1.1 (CRYSTAL_1)
PB2: IC1.5 ((PCINT10/ADC8/CLKO/TOCC7/ICP2/RXD0)_PB2)
RESET: IC1.4 ((PCINT11/ADC9/!RESET!/DW)_PB3), J3.A3, R2.1
SCK/SCL: IC1.9 (PA4_(PCINT4/ADC4/AIN11/TOCC3/T1/RXD1/SC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), J3.A2
SCL: J1.1, J2.1
SDA: J1.2, J2.2
VCC: C2.+, C3.2, IC3.3 (INPUT), J1.3, J2.3

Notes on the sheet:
Power Supply
Grove Connectors
